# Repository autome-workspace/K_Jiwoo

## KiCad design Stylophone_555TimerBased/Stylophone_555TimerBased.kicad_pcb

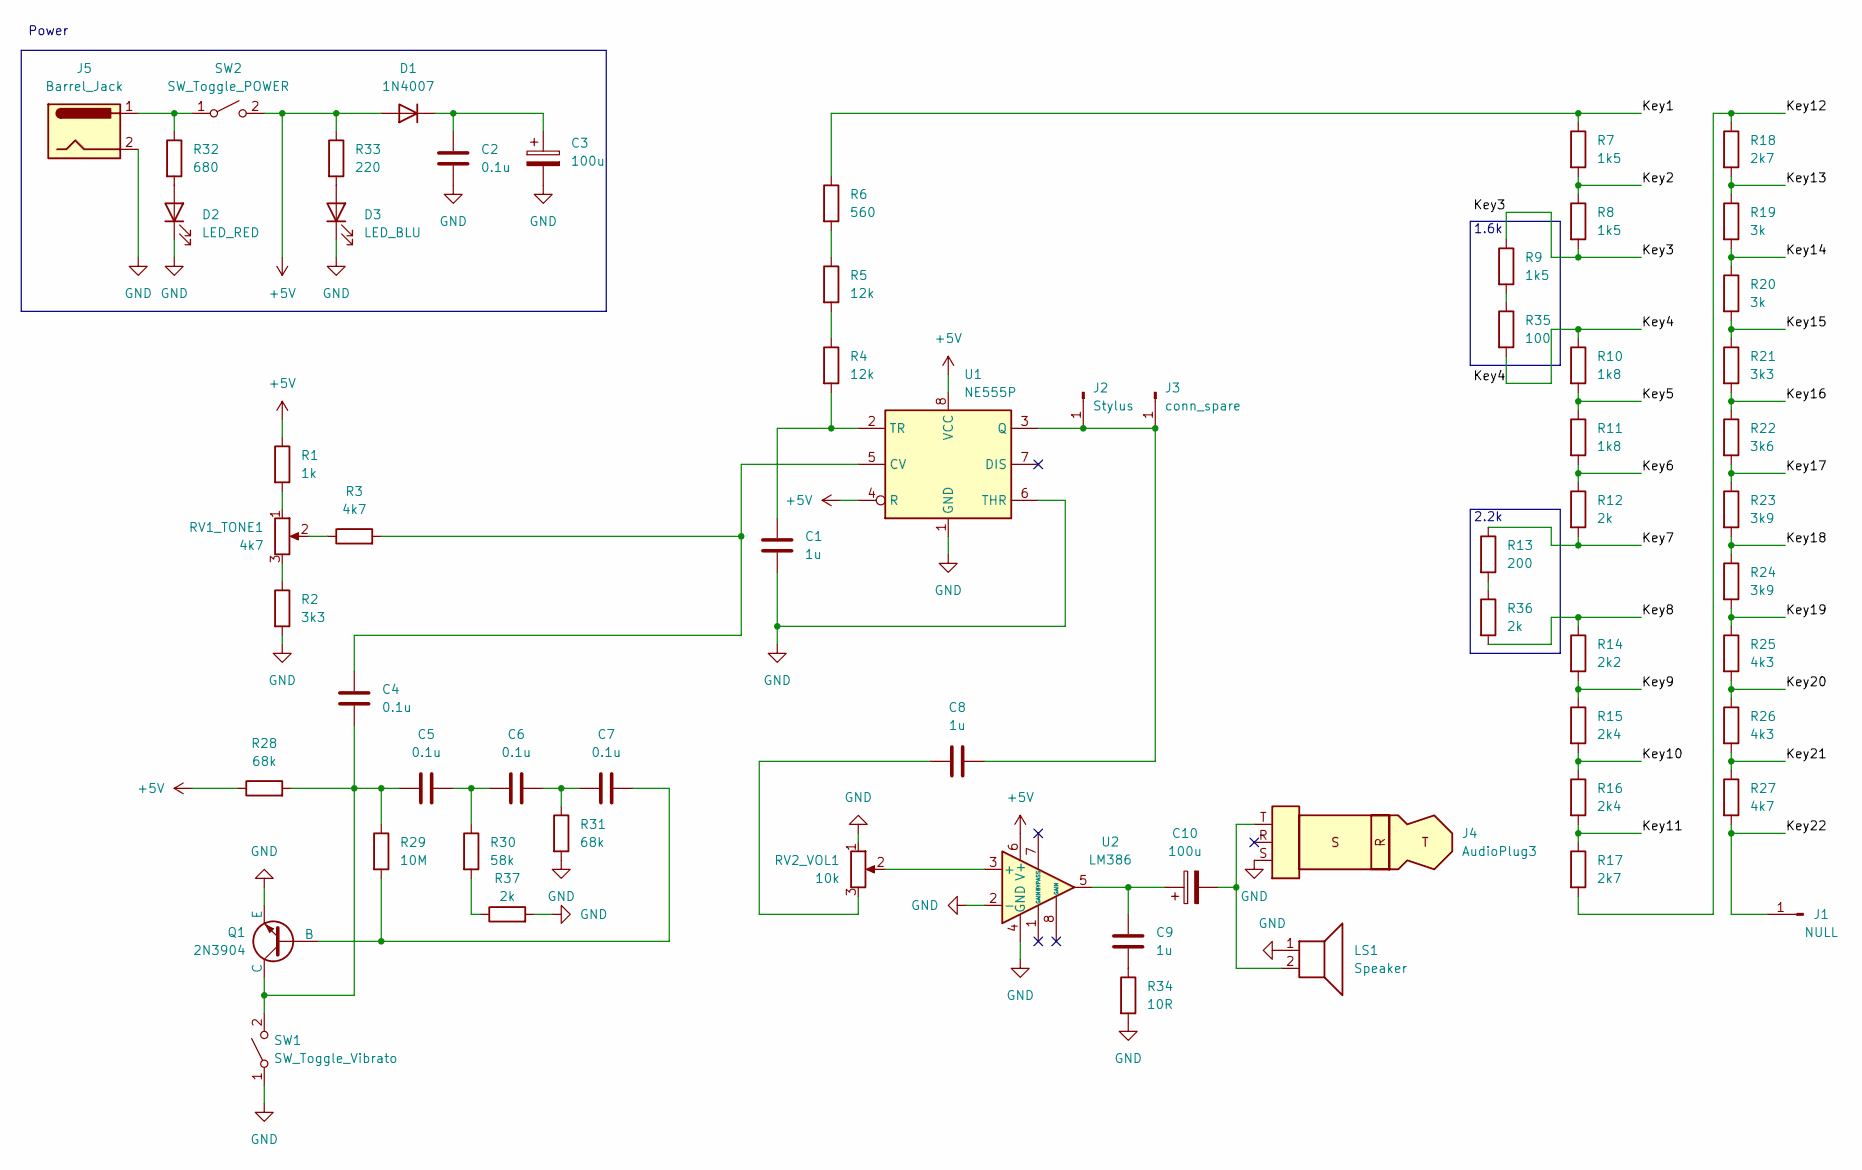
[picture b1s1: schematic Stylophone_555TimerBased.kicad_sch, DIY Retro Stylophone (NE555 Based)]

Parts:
C1, C8, C9: 1u; C_Rect_L7.2mm_W2.5mm_P5.00mm_FKS2_FKP2_MKS2_MKP2
C2, C4, C5, C6, C7: 0.1u; C_Rect_L7.2mm_W2.5mm_P5.00mm_FKS2_FKP2_MKS2_MKP2
C3, C10: 100u; CP_Radial_D5.0mm_P2.00mm
D1: 1N4007; D_DO-41_SOD81_P10.16mm_Horizontal
D2: LED_RED; LED_0603_1608Metric
D3: LED_BLU; LED_0603_1608Metric
J1: NULL; PinHeader_1x01_P2.54mm_Vertical
J2: Stylus; PinHeader_1x01_P2.54mm_Vertical
J3: conn_spare; PinHeader_1x01_P2.54mm_Vertical
J4: AudioPlug3; Jack_3.5mm_Switronic_ST-005-G_horizontal
J5: Barrel_Jack; BarrelJack_Horizontal
LS1: Speaker; JST_XH_B2B-XH-A_1x02_P2.50mm_Vertical
Q1: 2N3904; TO-92_Inline
R1: 1k; R_Axial_DIN0207_L6.3mm_D2.5mm_P7.62mm_Horizontal
R2, R21: 3k3; R_Axial_DIN0207_L6.3mm_D2.5mm_P7.62mm_Horizontal
R3, R27: 4k7; R_Axial_DIN0207_L6.3mm_D2.5mm_P7.62mm_Horizontal
R4, R5: 12k; R_Axial_DIN0207_L6.3mm_D2.5mm_P7.62mm_Horizontal
R6: 560; R_Axial_DIN0207_L6.3mm_D2.5mm_P7.62mm_Horizontal
R7, R8, R9: 1k5; R_Axial_DIN0207_L6.3mm_D2.5mm_P7.62mm_Horizontal
R10, R11: 1k8; R_Axial_DIN0207_L6.3mm_D2.5mm_P7.62mm_Horizontal
R12, R36, R37: 2k; R_Axial_DIN0207_L6.3mm_D2.5mm_P7.62mm_Horizontal
R13: 200; R_Axial_DIN0207_L6.3mm_D2.5mm_P7.62mm_Horizontal
R14: 2k2; R_Axial_DIN0207_L6.3mm_D2.5mm_P7.62mm_Horizontal
R15, R16: 2k4; R_Axial_DIN0207_L6.3mm_D2.5mm_P7.62mm_Horizontal
R17, R18: 2k7; R_Axial_DIN0207_L6.3mm_D2.5mm_P7.62mm_Horizontal
R19, R20: 3k; R_Axial_DIN0207_L6.3mm_D2.5mm_P7.62mm_Horizontal
R22: 3k6; R_Axial_DIN0207_L6.3mm_D2.5mm_P7.62mm_Horizontal
R23, R24: 3k9; R_Axial_DIN0207_L6.3mm_D2.5mm_P7.62mm_Horizontal
R25, R26: 4k3; R_Axial_DIN0207_L6.3mm_D2.5mm_P7.62mm_Horizontal
R28, R31: 68k; R_Axial_DIN0207_L6.3mm_D2.5mm_P7.62mm_Horizontal
R29: 10M; R_Axial_DIN0207_L6.3mm_D2.5mm_P7.62mm_Horizontal
R30: 58k; R_Axial_DIN0207_L6.3mm_D2.5mm_P7.62mm_Horizontal
R32: 680; R_0603_1608Metric
R33: 220; R_0603_1608Metric
R34: 10R; R_Axial_DIN0207_L6.3mm_D2.5mm_P7.62mm_Horizontal
R35: 100; R_Axial_DIN0207_L6.3mm_D2.5mm_P7.62mm_Horizontal
RV1_TONE1: 4k7; JST_XH_B3B-XH-A_1x03_P2.50mm_Vertical
RV2_VOL1: 10k; JST_XH_B3B-XH-A_1x03_P2.50mm_Vertical
SW1: SW_Toggle_Vibrato; PinHeader_1x03_P2.54mm_Vertical
SW2: SW_Toggle_POWER; PinHeader_1x03_P2.54mm_Vertical
U1: NE555P; DIP-8_W7.62mm_Socket
U2: LM386; DIP-8_W7.62mm_Socket

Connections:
+5V: D1.2 (A), R1.1, R28.1, R33.1, SW2.2 (B), U1.4 (R), U1.8 (VCC), U2.6 (V+)
/Key1: R6.1, R7.1
/Key2: R7.2, R8.1
/Key3: R8.2, R9.1
/Key4: R10.1, R35.2
/Key5: R10.2, R11.1
/Key6: R11.2, R12.1
/Key7: R12.2, R13.1
/Key8: R14.1, R36.2
/Key9: R14.2, R15.1
/Key10: R15.2, R16.1
/Key11: R16.2, R17.1
/Key12: R17.2, R18.1
/Key13: R18.2, R19.1
/Key14: R19.2, R20.1
/Key15: R20.2, R21.1
/Key16: R21.2, R22.1
/Key17: R22.2, R23.1
/Key18: R23.2, R24.1
/Key19: R24.2, R25.1
/Key20: R25.2, R26.1
/Key21: R26.2, R27.1
/Key22: J1.1, R27.2
GND: C1.2, C2.2, C3.2, D2.1 (K), D3.1 (K), J4.S, J5.2, LS1.1, Q1.3 (E), R2.2, R31.2, R34.2, R37.2, RV2_VOL1.1, SW1.1 (A), U1.1 (GND), U1.6 (THR), U2.2 (-), U2.4 (GND)
unnamed: C5.2, C6.1, R30.1
unnamed: C6.2, C7.1, R31.1
unnamed: C8.1, RV2_VOL1.3
unnamed: C9.1, R34.1
unnamed: C9.2, C10.1, U2.5
unnamed: C10.2, J4.T, LS1.2
unnamed: C2.1, C3.1, D1.1 (K)
unnamed: D2.2 (A), R32.2
unnamed: D3.2 (A), R33.2
unnamed: C8.2, J2.1, J3.1, U1.3 (Q)
unnamed: C7.2, Q1.2 (B), R29.2
unnamed: C4.2, C5.1, Q1.1 (C), R28.2, R29.1, SW1.2 (B)
unnamed: R1.2, RV1_TONE1.1
unnamed: R2.1, RV1_TONE1.3
unnamed: R3.1, RV1_TONE1.2
unnamed: R4.1, R5.2
unnamed: R5.1, R6.2
unnamed: R13.2, R36.1
unnamed: R30.2, R37.1
unnamed: R9.2, R35.1
unnamed: J5.1, R32.1, SW2.1 (A)
unnamed: C4.1, R3.2, U1.5 (CV)
unnamed: C1.1, R4.2, U1.2 (TR)
unnamed: RV2_VOL1.2, U2.3 (+)

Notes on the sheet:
2.2k
1.6k
Power

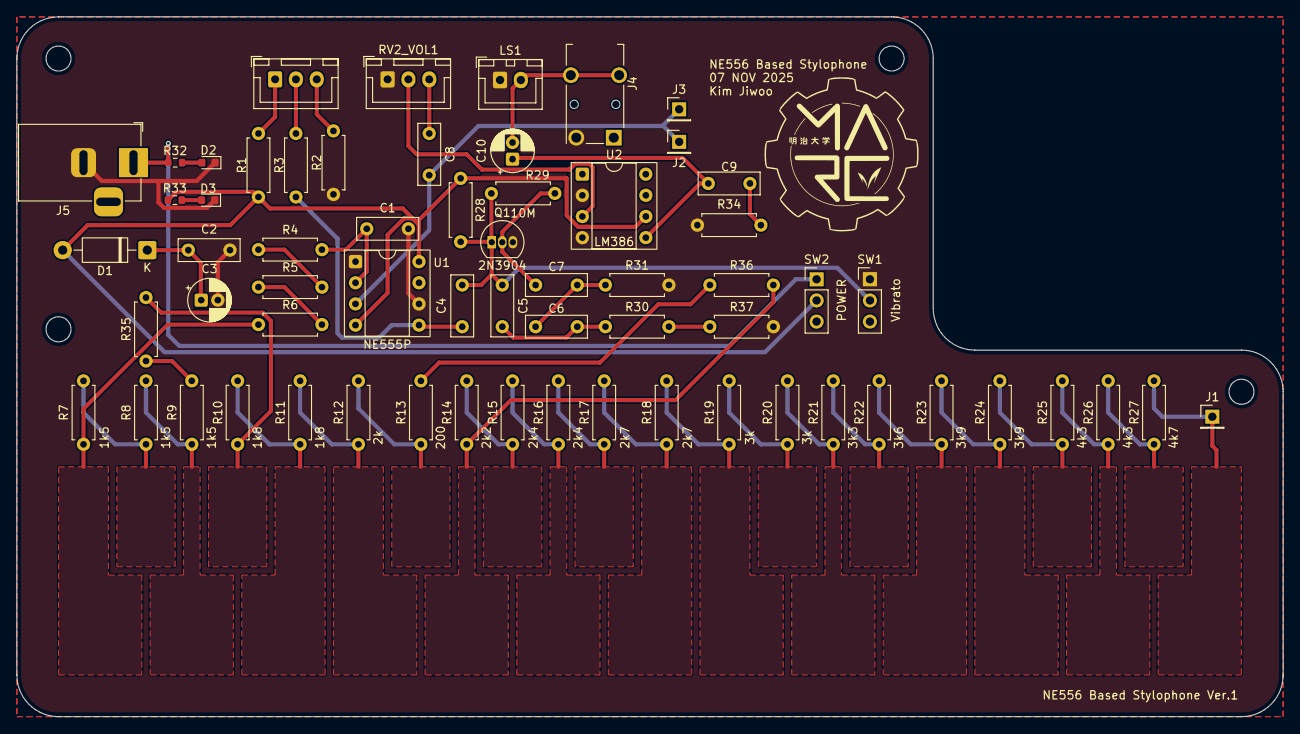
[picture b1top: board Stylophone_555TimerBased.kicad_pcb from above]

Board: 2 copper layers, 152.0 x 84.0 mm, 63 parts (0 on the bottom side), 48 nets.

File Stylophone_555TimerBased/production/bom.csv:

Designator,Footprint,Quantity,Value,LCSC Part #
"C1, C8, C9",C_Rect_L7.2mm_W2.5mm_P5.00mm_FKS2_FKP2_MKS2_MKP2,3,1u,
"C10, C3",CP_Radial_D5.0mm_P2.00mm,2,100u,
"C2, C4, C5, C6, C7",C_Rect_L7.2mm_W2.5mm_P5.00mm_FKS2_FKP2_MKS2_MKP2,5,0.1u,
D1,D_DO-41_SOD81_P10.16mm_Horizontal,1,1N4007,
D2,0603,1,LED_RED,
D3,0603,1,LED_BLU,
J1,PinHeader_1x01_P2.54mm_Vertical,1,NULL,
J2,PinHeader_1x01_P2.54mm_Vertical,1,Stylus,
J3,PinHeader_1x01_P2.54mm_Vertical,1,Spare,
J4,Jack_3.5mm_Switronic_ST-005-G_horizontal,1,AudioPlug3,
J5,BarrelJack_Horizontal,1,Barrel_Jack,
LS1,JST_XH_B2B-XH-A_1x02_P2.50mm_Vertical,1,Speaker,
Q1,TO-92_Inline,1,2N3904,
R1,R_Axial_DIN0207_L6.3mm_D2.5mm_P7.62mm_Horizontal,1,1k,
"R10, R11",R_Axial_DIN0207_L6.3mm_D2.5mm_P7.62mm_Horizontal,2,1k8,
"R12, R36, R37",R_Axial_DIN0207_L6.3mm_D2.5mm_P7.62mm_Horizontal,3,2k,
R13,R_Axial_DIN0207_L6.3mm_D2.5mm_P7.62mm_Horizontal,1,200,
R14,R_Axial_DIN0207_L6.3mm_D2.5mm_P7.62mm_Horizontal,1,2k2,
"R15, R16",R_Axial_DIN0207_L6.3mm_D2.5mm_P7.62mm_Horizontal,2,2k4,
"R17, R18",R_Axial_DIN0207_L6.3mm_D2.5mm_P7.62mm_Horizontal,2,2k7,
"R19, R20",R_Axial_DIN0207_L6.3mm_D2.5mm_P7.62mm_Horizontal,2,3k,
"R2, R21",R_Axial_DIN0207_L6.3mm_D2.5mm_P7.62mm_Horizontal,2,3k3,
R22,R_Axial_DIN0207_L6.3mm_D2.5mm_P7.62mm_Horizontal,1,3k6,
"R23, R24",R_Axial_DIN0207_L6.3mm_D2.5mm_P7.62mm_Horizontal,2,3k9,
"R25, R26",R_Axial_DIN0207_L6.3mm_D2.5mm_P7.62mm_Horizontal,2,4k3,
"R27, R3",R_Axial_DIN0207_L6.3mm_D2.5mm_P7.62mm_Horizontal,2,4k7,
"R28, R31",R_Axial_DIN0207_L6.3mm_D2.5mm_P7.62mm_Horizontal,2,68k,
R29,R_Axial_DIN0207_L6.3mm_D2.5mm_P7.62mm_Horizontal,1,10M,
R30,R_Axial_DIN0207_L6.3mm_D2.5mm_P7.62mm_Horizontal,1,58k,
R32,0603,1,680,
R33,0603,1,220,
R34,R_Axial_DIN0207_L6.3mm_D2.5mm_P7.62mm_Horizontal,1,10R,
R35,R_Axial_DIN0207_L6.3mm_D2.5mm_P7.62mm_Horizontal,1,100,
"R4, R5",R_Axial_DIN0207_L6.3mm_D2.5mm_P7.62mm_Horizontal,2,12k,
R6,R_Axial_DIN0207_L6.3mm_D2.5mm_P7.62mm_Horizontal,1,560,
"R7, R8, R9",R_Axial_DIN0207_L6.3mm_D2.5mm_P7.62mm_Horizontal,3,1k5,
RV1_TONE1,JST_XH_B3B-XH-A_1x03_P2.50mm_Vertical,1,4k7,
RV2_VOL1,JST_XH_B3B-XH-A_1x03_P2.50mm_Vertical,1,10k,
SW1,PinHeader_1x03_P2.54mm_Vertical,1,Vibrato,
SW2,PinHeader_1x03_P2.54mm_Vertical,1,POWER,
U1,DIP-8_W7.62mm_Socket,1,NE555P,
U2,DIP-8_W7.62mm_Socket,1,LM386,

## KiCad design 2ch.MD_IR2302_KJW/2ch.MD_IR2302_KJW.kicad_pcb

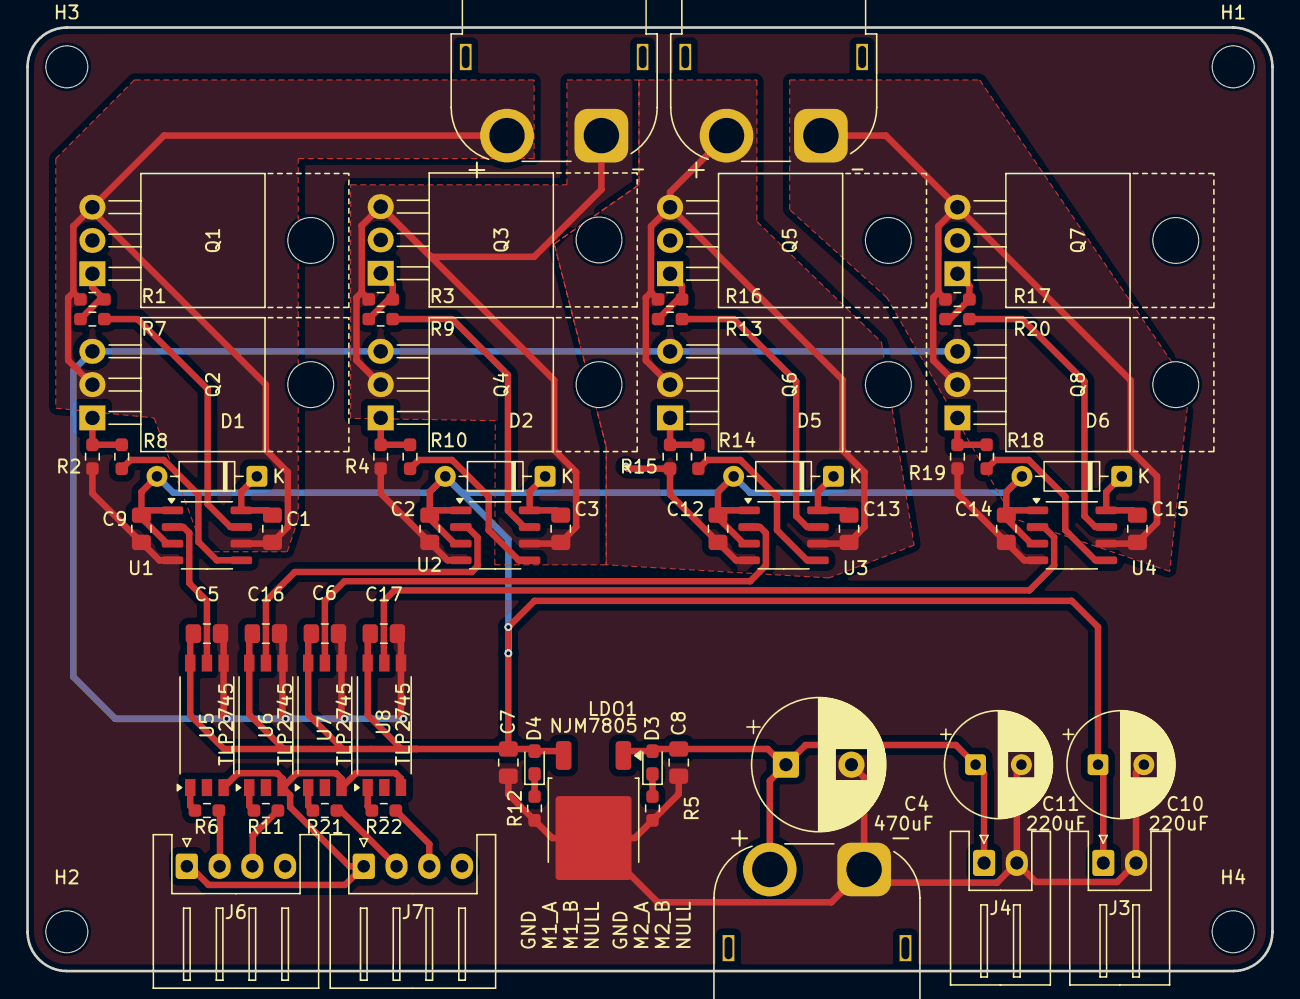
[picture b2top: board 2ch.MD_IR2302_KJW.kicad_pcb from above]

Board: 2 copper layers, 95.0 x 72.0 mm, 73 parts (0 on the bottom side), 42 nets.

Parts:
C1, C3, C13, C15: 10uF; C_0805_2012Metric_Pad1.18x1.45mm_HandSolder
C2, C5, C6, C7, C9, C12, C14, C16, C17: 0.1uF; C_0805_2012Metric_Pad1.18x1.45mm_HandSolder
C4: 470uF; CP_Radial_D10.0mm_P5.00mm
C8: 0.47uF; C_0805_2012Metric_Pad1.18x1.45mm_HandSolder
C10, C11: 220uF; CP_Radial_D8.0mm_P3.50mm
D1, D2, D5, D6: 1N4148; D_DO-35_SOD27_P7.62mm_Horizontal
D3, D4: LED; D_0603_1608Metric_Pad1.05x0.95mm_HandSolder
H1, H2, H3, H4: MountingHole; MountingHole_3.2mm_M3
J1, J2: XT60_Female_Horizontal; AMASS_XT60PW-F_1x02_P7.20mm_Horizontal
J3, J4: XH_01x02_Vertical; JST_XH_S2B-XH-A_1x02_P2.50mm_Horizontal
J5: XT60_Male_Horizontal; AMASS_XT60PW-M_1x02_P7.20mm_Horizontal
J6, J7: Conn_01x04_Pin; JST_XH_S4B-XH-A_1x04_P2.50mm_Horizontal
LDO1: NJM7805; TO-252-2
Q1, Q2, Q3, Q4, Q5, Q6, Q7, Q8: TK7R4A10PL_TabUp; TO-220-3_Horizontal_TabUp
R1, R2, R3, R4, R15, R16, R17, R19: R47k; R_0603_1608Metric_Pad0.98x0.95mm_HandSolder
R5, R12: R3k; R_0603_1608Metric_Pad0.98x0.95mm_HandSolder
R6, R11, R21, R22: 470; R_0603_1608Metric_Pad0.98x0.95mm_HandSolder
R7, R8, R9, R10, R13, R14, R18, R20: 4.7; R_0603_1608Metric_Pad0.98x0.95mm_HandSolder
U1, U2, U3, U4: IR2302; SOP-8_3.9x4.9mm_P1.27mm
U5, U6, U7, U8: TLP2745; SO-6L_10x3.84mm_P1.27mm

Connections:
+5V: C2.2, C5.2, C6.2, C7.2, C9.2, C10.1, C12.2, C14.2, C16.2, C17.2, D1.2 (A), D2.2 (A), D4.2 (A), D5.2 (A), D6.2 (A), J3.1, LDO1.3 (VOUT), U1.1 (VCC), U1.3 (~SD), U2.1 (VCC), U2.3 (~SD), U3.1 (VCC), U3.3 (~SD), U4.1 (VCC), U4.3 (~SD), U5.6 (VDD), U6.6 (VDD), U7.6 (VDD), U8.6 (VDD)
GND: C2.1, C4.2, C5.1, C6.1, C7.1, C8.2, C9.1, C10.2, C11.2, C12.1, C14.1, C16.1, C17.1, J3.2, J4.2, J5.1 (GND), LDO1.2 (GND), Q2.3 (S), Q4.3 (S), Q6.3 (S), Q8.3 (S), R2.2, R4.2, R5.1, R12.1, R15.2, R19.2, U1.4 (COM), U2.4 (COM), U3.4 (COM), U4.4 (COM), U5.4 (GND), U6.4 (GND), U7.4 (GND), U8.4 (GND)
GND_ESP: J6.1, J7.1, U5.3 (K), U6.3 (K), U7.3 (K), U8.3 (K)
IN_A1: J6.2, R6.2
IN_A2: J6.3, R11.1
IN_B1: J7.2, R21.2
IN_B2: J7.3, R22.1
Motor_A_Minus: C3.2, J1.1 (GND), Q3.3 (S), Q4.2 (D), R3.2, U2.6 (VS)
Motor_A_Plus: C1.2, J1.2 (VOUT), Q1.3 (S), Q2.2 (D), R1.2, U1.6 (VS)
Motor_B_Minus: C15.2, J2.1 (GND), Q7.3 (S), Q8.2 (D), R17.2, U4.6 (VS)
Motor_B_Plus: C13.2, J2.2 (VOUT), Q5.3 (S), Q6.2 (D), R16.2, U3.6 (VS)
unnamed: C1.1, D1.1 (K), U1.8 (VB)
unnamed: C3.1, D2.1 (K), U2.8 (VB)
unnamed: D3.1 (K), R5.2
unnamed: D4.1 (K), R12.2
unnamed: C13.1, D5.1 (K), U3.8 (VB)
unnamed: C15.1, D6.1 (K), U4.8 (VB)
unnamed: Q1.1 (G), R1.1, R7.2
unnamed: Q2.1 (G), R2.1, R8.2
unnamed: Q3.1 (G), R3.1, R9.1
unnamed: Q4.1 (G), R4.1, R10.1
unnamed: Q5.1 (G), R13.2, R16.1
unnamed: Q6.1 (G), R14.2, R15.1
unnamed: Q7.1 (G), R17.1, R20.1
unnamed: Q8.1 (G), R18.1, R19.1
unnamed: R6.1, U5.1 (A)
unnamed: R11.2, U6.1 (A)
unnamed: R21.1, U7.1 (A)
unnamed: R22.2, U8.1 (A)
U1_HO: R7.1, U1.7 (HO)
U1_IN: U1.2 (IN), U5.5 (VO)
U1_LO: R8.1, U1.5 (LO)
U2_HO: R9.2, U2.7 (HO)
U2_IN: U2.2 (IN), U6.5 (VO)
U2_LO: R10.2, U2.5 (LO)
U3_HO: R13.1, U3.7 (HO)
U3_IN: U3.2 (IN), U7.5 (VO)
U3_LO: R14.1, U3.5 (LO)
U4_HO: R20.2, U4.7 (HO)
U4_IN: U4.2 (IN), U8.5 (VO)
U4_LO: R18.2, U4.5 (LO)
VCC: C4.1, C8.1, C11.1, D3.2 (A), J4.1, J5.2 (VIN), LDO1.1 (VIN), Q1.2 (D), Q3.2 (D), Q5.2 (D), Q7.2 (D)

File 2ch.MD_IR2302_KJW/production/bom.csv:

Designator,Footprint,Quantity,Value,LCSC Part #
"C1, C13, C15, C3",0805,4,10uF,
"C10, C11",CP_Radial_D8.0mm_P3.50mm,2,220uF,
"C12, C14, C16, C17, C2, C5, C6, C7, C9",0805,9,0.1uF,
C4,CP_Radial_D10.0mm_P5.00mm,1,470uF,
C8,0805,1,0.47uF,
"D1, D2, D5, D6",D_DO-35_SOD27_P7.62mm_Horizontal,4,1N4148,
"D3, D4",0603,2,LED,
"J1, J2",AMASS_XT60PW-F_1x02_P7.20mm_Horizontal,2,XT60_Female_Horizontal,
"J3, J4",JST_XH_S2B-XH-A_1x02_P2.50mm_Horizontal,2,XH_01x02_Vertical,
J5,AMASS_XT60PW-M_1x02_P7.20mm_Horizontal,1,XT60_Male_Horizontal,
"J6, J7",JST_XH_S4B-XH-A_1x04_P2.50mm_Horizontal,2,Conn_01x04_Pin,
LDO1,TO-252-2,1,NJM7805,
"Q1, Q2, Q3, Q4, Q5, Q6, Q7, Q8",TO-220-3_Horizontal_TabUp,8,TK7R4A10PL_TabUp,
"R1, R15, R16, R17, R19, R2, R3, R4",0603,8,R47k,
"R10, R13, R14, R18, R20, R7, R8, R9",0603,8,4.7,
"R11, R21, R22, R6",0603,4,470,
"R12, R5",0603,2,R3k,
"U1, U2, U3, U4",SOP-8_3.9x4.9mm_P1.27mm,4,IR2302,
"U5, U6, U7, U8",SO-6L_10x3.84mm_P1.27mm,4,TLP2745,

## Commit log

2025-11-14 1Channel Motor Driver
2025-11-14 2channel motor driver
    2channel motor driver based IR2302
    https://partscabi.net/list/4a4d080e-9e87-4b8e-8b76-c81ae6719885
2025-11-14 Stylophone Ver. 1.0
    555 Timer based Stylophone
